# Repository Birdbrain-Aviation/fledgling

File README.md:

# Fledgling

> **Status: work in progress (WIP).** The schematic is drawn and the board is fully routed and passes KiCad's design-rule check (0 errors, 0 unconnected items), but the design is **not reviewed electrically, not fabricated and not tested.** Nothing here has flown. I'm publishing it as it stands.

Fledgling is a small single-MCU flight computer for my model and high-power rockets. It's meant to be a simpler sibling of my CORVID flight computer: the same RP2350 family, IMU and power parts, so firmware and drivers carry over. It is designed to work with the [Aviary](https://github.com/Birdbrain-Aviation/aviary) software suite (Owl ground station, Heron log analysis, Mockingbird hardware-in-the-loop testing).

## Board views

These are rendered from the board file by `tools/render_board.py` (copper, pads and vias only; the inner planes are not drawn), so they are not KiCad screenshots.

## Design intent

These are the goals from my design notes, not verified results.

- Detect launch, burnout and apogee from a barometer and an IMU on one RP2350A
- Fire up to two pyro channels (deployment, backup deployment, or staged-motor ignition)
- Drive two servo outputs on a 5 V rail (airbrakes on my American Rocketry Challenge rocket)
- Log flight data to onboard flash for later analysis in Heron
- Send downlink-only telemetry over an E220 LoRa module (the rocket never receives commands)
- Report status with three LEDs, four addressable RGB LEDs and a buzzer
- Measure a load cell through a 24-bit ADC

Safety approach (as designed, unproven): pyro outputs are held off by gate pull-downs at power-up and reset, pyro has its own battery and a screw arming switch, and firmware ignores pyro until launch is detected.

## Hardware

| | |
|---|---|
| Board | 90 x 40 mm, 4 copper layers (signal / GND / +3V3 / signal), KiCad 10 |
| MCU | RP2350A, W25Q128JVSIQ 16 MB QSPI flash |
| Sensors | MS5611 barometer, LSM6DSO32 IMU, NAU7802 load-cell ADC |
| Radio | E220-900T22D LoRa module (915 MHz) on an 8-pin JST-GH cable |
| Power | Two XT30 battery inputs (main and pyro), two AP63301 buck converters (3.3 V and 5 V), reverse-polarity FET, fuses, TVS diodes |
| Outputs | 2 pyro channels (IRLR7843 low-side MOSFETs), 2 servo headers, 4x WS2812B, buzzer |
| I/O | USB-C, SWD header, I2C OLED header, load-cell header, BOOTSEL and reset buttons |

The schematic has a top-level sheet (`Fledgling.kicad_sch`) and four sub-sheets: Power, IO, Sensors and Pyro. The Pyro sheet is stored in `untitled.kicad_sch`; I left that filename alone so the sheet reference keeps working.

## Repository layout

```
hardware/   KiCad 10 project: schematic sheets, PCB, design rules
  libs/     custom footprint library (Fledgling.pretty)
bom/        parts list exported from my Google Sheet
docs/       DRC report, layout log, remaining-work list, images
tools/      script that renders the board views from the .kicad_pcb
```

Open `hardware/Fledgling.kicad_pro` in KiCad 10.

Symbols and footprints are embedded in the schematic and board files, so the design opens without the extra libraries. To edit parts you'll need the third-party libraries I used, which I haven't redistributed: Raspberry Pi's RP2350 minimal-design KiCad library (`RPI_DB`, `RPI_COMPILED`) and `easyeda2kicad`-converted parts.

## Known state (WIP)

- **2026-11-22: board fully routed, DRC clean.** KiCad 10.0.6 DRC with zones refilled (`docs/DRC-2026-11-22-final.rpt`): **0 errors, 0 unconnected items, 12 warnings.** All 12 warnings are footprint-library mismatches or footprints missing from the `Fledgling` library; they predate the routing. The only part that moved is L1 (0.05 mm in y). The routing was produced with scripts (a grid router and a local checker, not in this repo) and then checked in KiCad, so **nobody has reviewed it electrically**: buck-converter loops, USB pair, QSPI, the ADC dividers and the pyro sense tap still need a human look. Details are in `docs/design-decisions.md` section 11.
- Gerbers and drills for this version are in `fab/Fledgling-gerbers-2026-11-22.zip`. They are DRC-clean but **not yet checked by a fab's CAM or ordered.** Get a quote and a CAM check before ordering.
- The previous version (22 errors / 22 unconnected power connections) is kept in `hardware/archive/Fledgling_routed_2026-11-21.kicad_pcb`.
- Changes on 2026-11-17: E220 supply (J2 pin 6) moved from +5V to +3V3, with the +5V trunk re-routed under J2 on B.Cu; C35/C36 feed-forward capacitor values set. See `docs/design-decisions.md`.
- Connector orientation (USB-C and XT30) checked. See `docs/layout-log-2026-11-14.md` and `docs/design-decisions.md` for the full history.
- The BOM is a draft. Some prices are optimistic LCSC "from" prices, some parts are marked pending (pyro fuse rating, load cell capacity), and a few parts have low stock. See the Status and Notes columns in `bom/Fledgling_BOM.csv`.
- Routing is complete but machine-generated and untidy in places (many small jogs near the RP2350).
- The design has changed since my first sketches (it started as a 30 x 80 mm 2-layer board), so the early notes don't all match the current board.

## License

Not yet specified.

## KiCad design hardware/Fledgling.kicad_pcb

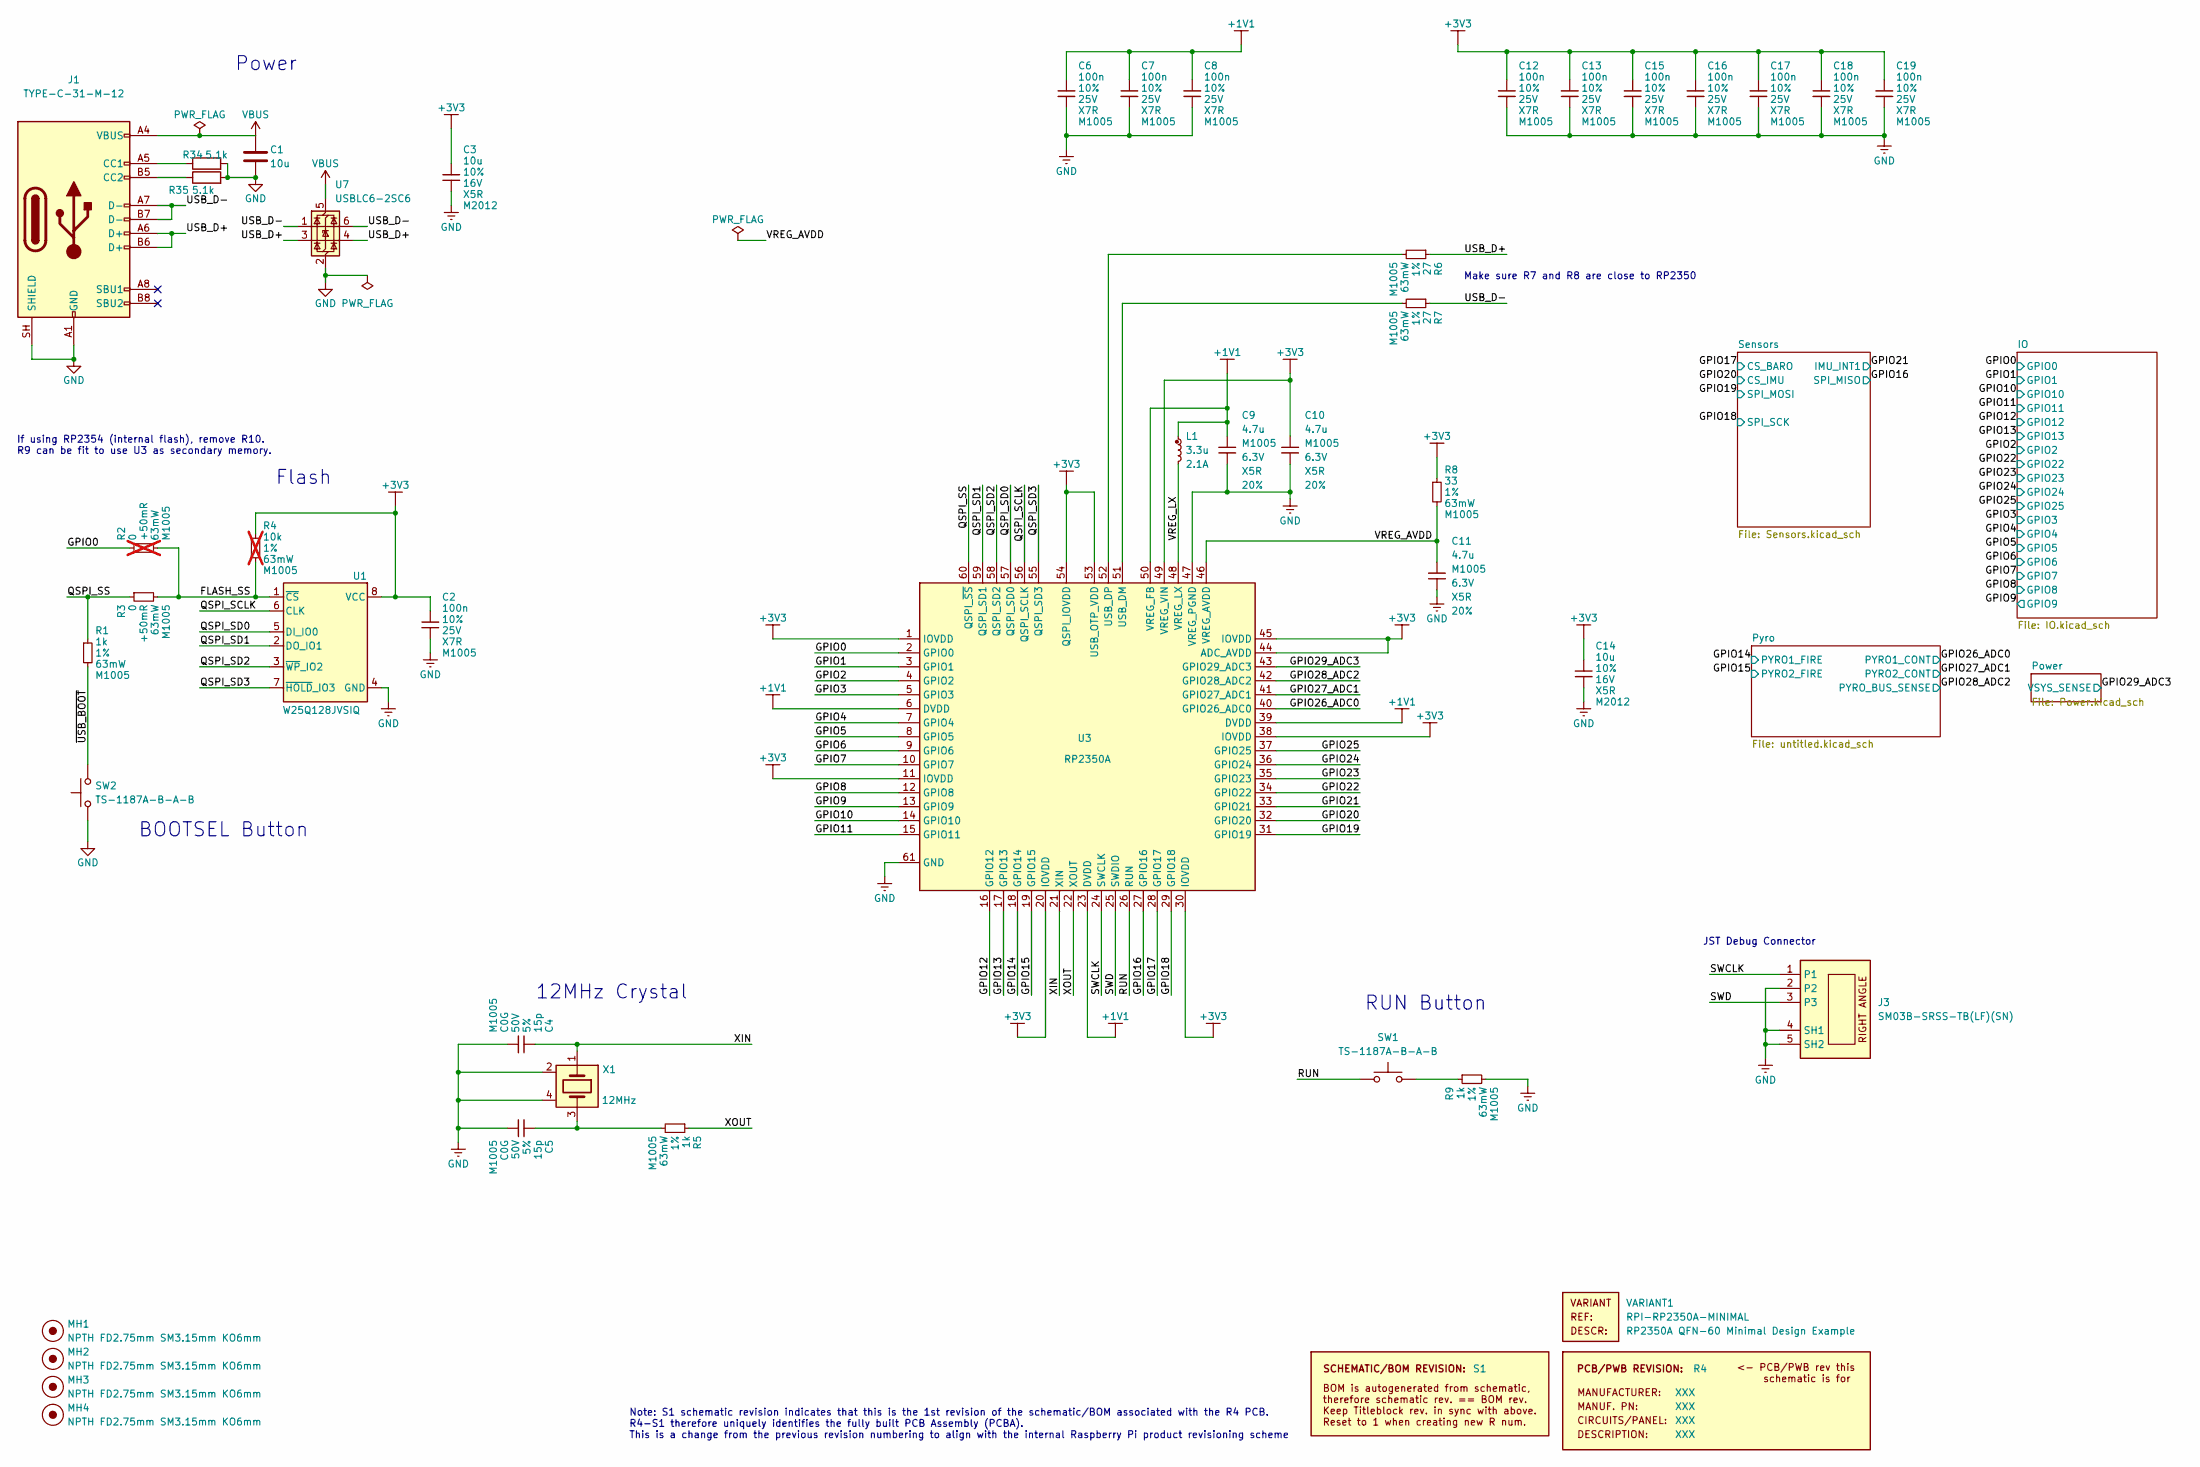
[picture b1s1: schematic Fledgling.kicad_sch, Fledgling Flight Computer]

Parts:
C1: 10u; C_0805_2012Metric; LCSC Part C15850
C2, C6, C7, C8, C12, C13, C15, C16, C17, C18, C19: 100n; generic_capc1005x50; voltage 25V; tolerance 10%; part_uid RP-01BJ9Y-KRGF41; lcsc_pn C77014
C3, C14: 10u; generic_capc2012x125; voltage 16V; tolerance 10%; part_uid RP-01GYSK-AVBE41; lcsc_pn C77075
C4, C5: 15p; generic_capc1005x50; voltage 50V; tolerance 5%; part_uid RP-01C89W-LLY9XV; lcsc_pn C76950
C9, C10: 4.7u; generic_capc1005x50_wide; voltage 6.3V; tolerance 20%; part_uid RP-019A1P-0C2GHY; lcsc_pn C82453
C11: 4.7u; generic_capc1005x50; voltage 6.3V; tolerance 20%; part_uid RP-019A1P-0C2GHY; lcsc_pn C82453
J1: TYPE-C-31-M-12; USB_C_Receptacle_HRO_TYPE-C-31-M-12; LCSC Part C165948
J3: SM03B-SRSS-TB(LF)(SN); jst_sm03b-srss-tb-lf--sn-; part_uid RP-01EKJ1-8V9SV1; LCSC Part C3029342
L1: 3.3u; abracon_aota-b201610s3r3-101-t; tolerance 20%; part_uid RP-01GY5D-2VC7WP; lcsc_pn C42411119
MH1, MH2, MH3, MH4: NPTH FD2.75mm SM3.15mm KO6mm; none_mh_npth_fd2p75mm_sm3p15mm_ko6mm; part_uid RP-01HF5R-LCTEJS
PCB1: R4; manufacturer_pn XXX
R1, R5, R9: 1k; generic_resc1005x35; tolerance 1%; voltage 50V; part_uid RP-019A1P-4Z6ZWY; lcsc_pn C106235
R2: 0; generic_resc1005x35; tolerance +50mR; voltage 50V; part_uid RP-019A1P-4Y4V63; lcsc_pn C60485; not fitted
R3: 0; generic_resc1005x35; tolerance +50mR; voltage 50V; part_uid RP-019A1P-4Y4V63; lcsc_pn C60485
R4: 10k; generic_resc1005x35; tolerance 1%; voltage 50V; part_uid RP-019A1P-53DHSX; lcsc_pn C60490; not fitted
R6, R7: 27; generic_resc1005x35; tolerance 1%; voltage 50V; part_uid RP-01C89V-LTEYC4; lcsc_pn C138021
R8: 33; generic_resc1005x35; tolerance 1%; voltage 50V; part_uid RP-019A1P-58PW9L; lcsc_pn C138002
R34, R35: 5.1k; R_0603_1608Metric; LCSC Part C23186
SBREV1: S1
SW1, SW2: TS-1187A-B-A-B; SW_Push_1P1T_XKB_TS-1187A; LCSC Part C318884
U1: W25Q128JVSIQ; generic_soic127p790x195-8; voltage 2.7-3.6V; part_uid RP-01JWD4-F1H4N9; lcsc_pn C97521
U3: RP2350A; rpi_rp2350a_vias; part_uid RP-01HA9H-9K5E8T; lcsc_pn C42411118
U7: USBLC6-2SC6; SOT-23-6; LCSC Part C7519
VARIANT1: RPI-RP2350A-MINIMAL
X1: 12MHz; generic_xtalcc320x250x80-4; tolerance 30ppm; part_uid RP-01G8X7-GS352B; lcsc_pn C20625731

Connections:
+1V1: C6.1, C7.1, C8.1, C9.1, L1.1, U3.6 (DVDD), U3.23 (DVDD), U3.39 (DVDD), U3.50 (VREG_FB)
+3V3: C2.1, C3.1, C10.1, C12.1, C13.1, C14.1, C15.1, C16.1, C17.1, C18.1, C19.1, R4.1, R8.1, U1.8 (VCC), U3.1 (IOVDD), U3.11 (IOVDD), U3.20 (IOVDD), U3.30 (IOVDD), U3.38 (IOVDD), U3.44 (ADC_AVDD), U3.45 (IOVDD), U3.49 (VREG_VIN), U3.53 (USB_OTP_VDD), U3.54 (QSPI_IOVDD); also elsewhere on the board
/FLASH_SS: R2.2, R3.2, R4.2, U1.1 (~CS)
/GPIO0: R2.1, U3.2 (GPIO0); also elsewhere on the board
/GPIO1: U3.3 (GPIO1); also elsewhere on the board
/GPIO2: U3.4 (GPIO2); also elsewhere on the board
/GPIO3: U3.5 (GPIO3); also elsewhere on the board
/GPIO4: U3.7 (GPIO4); also elsewhere on the board
/GPIO5: U3.8 (GPIO5); also elsewhere on the board
/GPIO6: U3.9 (GPIO6); also elsewhere on the board
/GPIO7: U3.10 (GPIO7); also elsewhere on the board
/GPIO8: U3.12 (GPIO8); also elsewhere on the board
/GPIO9: U3.13 (GPIO9); also elsewhere on the board
/GPIO10: U3.14 (GPIO10); also elsewhere on the board
/GPIO11: U3.15 (GPIO11); also elsewhere on the board
/GPIO12: U3.16 (GPIO12); also elsewhere on the board
/GPIO13: U3.17 (GPIO13); also elsewhere on the board
/GPIO14: U3.18 (GPIO14); also elsewhere on the board
/GPIO15: U3.19 (GPIO15); also elsewhere on the board
/GPIO16: U3.27 (GPIO16); also elsewhere on the board
/GPIO17: U3.28 (GPIO17); also elsewhere on the board
/GPIO18: U3.29 (GPIO18); also elsewhere on the board
/GPIO19: U3.31 (GPIO19); also elsewhere on the board
/GPIO20: U3.32 (GPIO20); also elsewhere on the board
/GPIO21: U3.33 (GPIO21); also elsewhere on the board
/GPIO22: U3.34 (GPIO22); also elsewhere on the board
/GPIO23: U3.35 (GPIO23); also elsewhere on the board
/GPIO24: U3.36 (GPIO24); also elsewhere on the board
/GPIO25: U3.37 (GPIO25); also elsewhere on the board
/GPIO26_ADC0: U3.40 (GPIO26_ADC0); also elsewhere on the board
/GPIO27_ADC1: U3.41 (GPIO27_ADC1); also elsewhere on the board
/GPIO28_ADC2: U3.42 (GPIO28_ADC2); also elsewhere on the board
/GPIO29_ADC3: U3.43 (GPIO29_ADC3); also elsewhere on the board
/QSPI_SCLK: U1.6 (CLK), U3.56 (QSPI_SCLK)
/QSPI_SD0: U1.5 (DI_IO0), U3.57 (QSPI_SD0)
/QSPI_SD1: U1.2 (DO_IO1), U3.59 (QSPI_SD1)
/QSPI_SD2: U1.3 (~WP_IO2), U3.58 (QSPI_SD2)
/QSPI_SD3: U1.7 (~HOLD_IO3), U3.55 (QSPI_SD3)
/QSPI_SS: R1.1, R3.1, U3.60 (QSPI_~SS)
/RUN: SW1.1, U3.26 (RUN)
/SWCLK: J3.1, U3.24 (SWCLK)
/SWD: J3.3, U3.25 (SWDIO)
/USB_D+: J1.A6 (D+), J1.B6 (D+), R6.1, U7.3 (I/O2), U7.4 (I/O2)
/USB_D-: J1.A7 (D-), J1.B7 (D-), R7.1, U7.1 (I/O1), U7.6 (I/O1)
/VREG_AVDD: C11.1, R8.2, U3.46 (VREG_AVDD)
/VREG_LX: L1.2, U3.48 (VREG_LX)
/XIN: C4.1, U3.21 (XIN), X1.1
/XOUT: R5.1, U3.22 (XOUT)
/~USB_BOOT: R1.2, SW2.2
GND: C1.2, C2.2, C3.2, C4.2, C5.2, C6.2, C7.2, C8.2, C9.2, C10.2, C11.2, C12.2, C13.2, C14.2, C15.2, C16.2, C17.2, C18.2, C19.2, J1.A1 (GND), J1.A12 (GND), J1.B1 (GND), J1.B12 (GND), J1.SH (SHIELD), J3.2, J3.4 (SH1), J3.5 (SH2), R9.2, R34.2, R35.2, SW2.1, U1.4 (GND), U3.47 (VREG_PGND), U3.61 (GND), U7.2 (GND), X1.2, X1.4; also elsewhere on the board
unnamed: C5.1, R5.2, X1.3
unnamed: J1.A5 (CC1), R34.1
unnamed: J1.B5 (CC2), R35.1
unnamed: R9.1, SW1.2
unnamed: R7.2, U3.51 (USB_DM)
unnamed: R6.2, U3.52 (USB_DP)
VBUS: C1.1, J1.A4 (VBUS), J1.A9 (VBUS), J1.B4 (VBUS), J1.B9 (VBUS), U7.5 (VBUS); also elsewhere on the board

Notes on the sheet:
JST Debug Connector
RUN Button
BOOTSEL Button
If using RP2354 (internal flash), remove R10. R9 can be fit to use U3 as secondary memory.
Flash
Note: S1 schematic revision indicates that this is the 1st revision of the schematic/BOM associated with the R4 PCB. R4-S1 therefore uniquely identifies the fully built PCB Assembly (PCBA). This is a change from the previous revision numbering to align with the internal Raspberry Pi product revisio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
Make sure R7 and R8 are close to RP2350
12MHz Crystal
Power

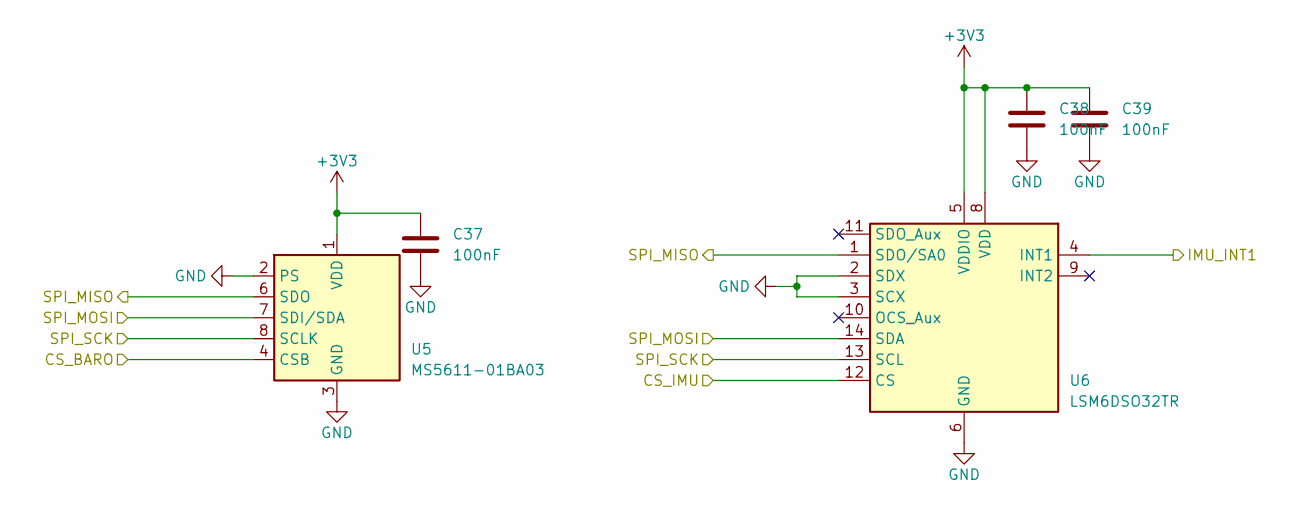
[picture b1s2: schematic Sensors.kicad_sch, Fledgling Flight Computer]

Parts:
C37, C38, C39: 100nF; C_0603_1608Metric; LCSC Part C1591
U5: MS5611-01BA03; LGA-8_3x5mm_P1.25mm; MPN MS561101BA03-50; LCSC Part C15639
U6: LSM6DSO32TR; LGA-14_3x2.5mm_P0.5mm_LayoutBorder3x4y; LCSC Part C1864162

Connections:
+3V3: C37.1, C38.1, C39.1, U5.1 (VDD), U6.5 (VDDIO), U6.8 (VDD); also elsewhere on the board
/GPIO16: U5.6 (SDO), U6.1 (SDO/SA0); also elsewhere on the board
/GPIO17: U5.4 (CSB), U5.5 (CSB); also elsewhere on the board
/GPIO18: U5.8 (SCLK), U6.13 (SCL); also elsewhere on the board
/GPIO19: U5.7 (SDI/SDA), U6.14 (SDA); also elsewhere on the board
/GPIO20: U6.12 (CS); also elsewhere on the board
/GPIO21: U6.4 (INT1); also elsewhere on the board
GND: C37.2, C38.2, C39.2, U5.2 (PS), U5.3 (GND), U6.2 (SDX), U6.3 (SCX), U6.6 (GND), U6.7 (GND); also elsewhere on the board

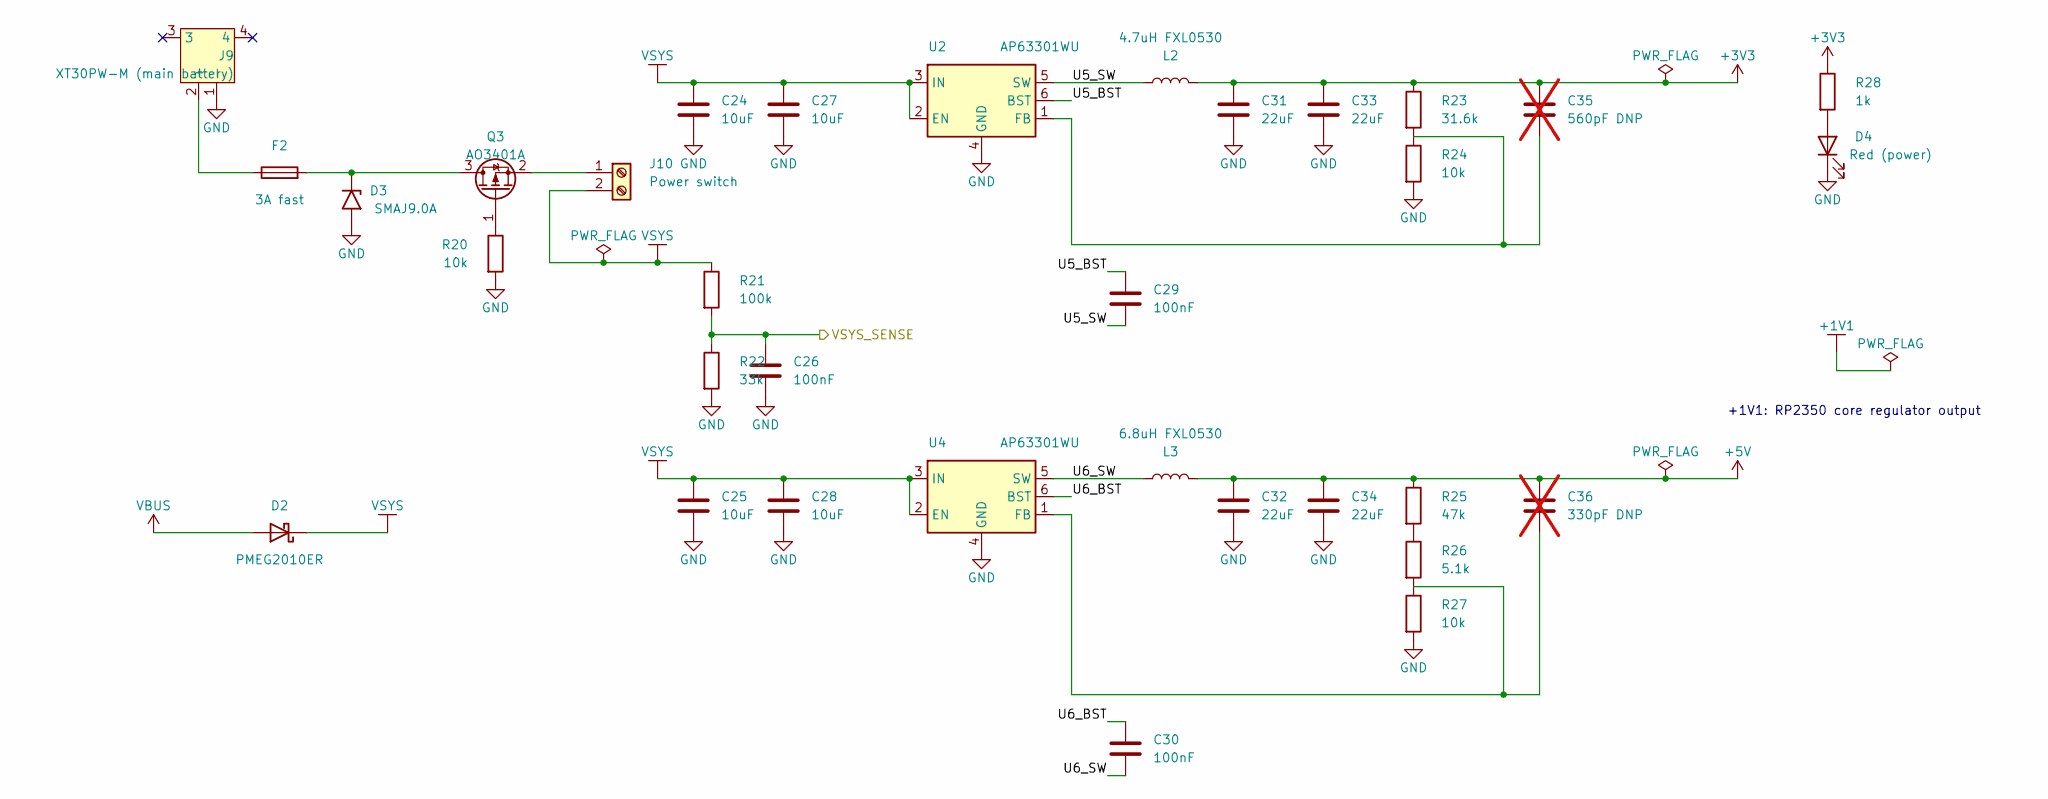
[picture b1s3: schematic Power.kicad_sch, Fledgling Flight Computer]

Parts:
C24, C25, C27, C28: 10uF; C_0805_2012Metric; Voltage 25V; LCSC Part C15850
C26, C29, C30: 100nF; C_0603_1608Metric; LCSC Part C1591
C31, C32, C33, C34: 22uF; C_0805_2012Metric; Voltage 10V; LCSC Part C92814
C35: 560pF DNP; C_0603_1608Metric; LCSC Part C55393; not fitted
C36: 330pF DNP; C_0603_1608Metric; LCSC Part C1664; not fitted
D2: PMEG2010ER; Nexperia_CFP3_SOD-123W; LCSC Part C82288
D3: SMAJ9.0A; D_SMA; LCSC Part C113955
D4: Red (power); LED_0603_1608Metric; LCSC Part C2286
F2: 3A fast; Fuse_1206_3216Metric; MPN 0466003.NRHF; LCSC Part C14165
J9: XT30PW-M (main battery); CONN-TH_XT30PW-M; MPN XT30PW-M30.G.Y; LCSC Part C431092
J10: Power switch; TerminalBlock_Phoenix_MKDS-1-2-3.81_1x02_P3.81mm_Horizontal; LCSC Part C395878
L2: 4.7uH FXL0530; L_Changjiang_FXL0530; LCSC Part C177246
L3: 6.8uH FXL0530; L_Changjiang_FXL0530; LCSC Part C177249
Q3: AO3401A; SOT-23; LCSC Part C347476
R20, R24, R27: 10k; R_0603_1608Metric; LCSC Part C25804
R21: 100k; R_0603_1608Metric; LCSC Part C25803
R22: 33k; R_0603_1608Metric; LCSC Part C4216
R23: 31.6k; R_0603_1608Metric; LCSC Part C25967
R25: 47k; R_0603_1608Metric; LCSC Part C25819
R26: 5.1k; R_0603_1608Metric; LCSC Part C23186
R28: 1k; R_0603_1608Metric; LCSC Part C21190
U2, U4: AP63301WU; TSOT-23-6; LCSC Part C2158003

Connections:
+3V3: C31.1, C33.1, C35.1, L2.2, R23.1, R28.1; also elsewhere on the board
+5V: C32.1, C34.1, C36.1, L3.2, R25.1; also elsewhere on the board
/GPIO29_ADC3: C26.1, R21.2, R22.1; also elsewhere on the board
/Power/U5_BST: C29.1, U2.6 (BST)
/Power/U5_SW: C29.2, L2.1, U2.5 (SW)
/Power/U6_BST: C30.1, U4.6 (BST)
/Power/U6_SW: C30.2, L3.1, U4.5 (SW)
GND: C24.2, C25.2, C26.2, C27.2, C28.2, C31.2, C32.2, C33.2, C34.2, D3.2 (A2), D4.1 (K), J9.1 (-), R20.2, R22.2, R24.2, R27.2, U2.4 (GND), U4.4 (GND); also elsewhere on the board
unnamed: D3.1 (A1), F2.2, Q3.3 (D)
unnamed: D4.2 (A), R28.2
unnamed: F2.1, J9.2 (+)
unnamed: J10.1, Q3.2 (S)
unnamed: Q3.1 (G), R20.1
unnamed: R25.2, R26.1
unnamed: C35.2, R23.2, R24.1, U2.1 (FB)
unnamed: C36.2, R26.2, R27.1, U4.1 (FB)
VBUS: D2.2 (A); also elsewhere on the board
VSYS: C24.1, C25.1, C27.1, C28.1, D2.1 (K), J10.2, R21.1, U2.2 (EN), U2.3 (IN), U4.2 (EN), U4.3 (IN)

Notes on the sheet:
+1V1: RP2350 core regulator output

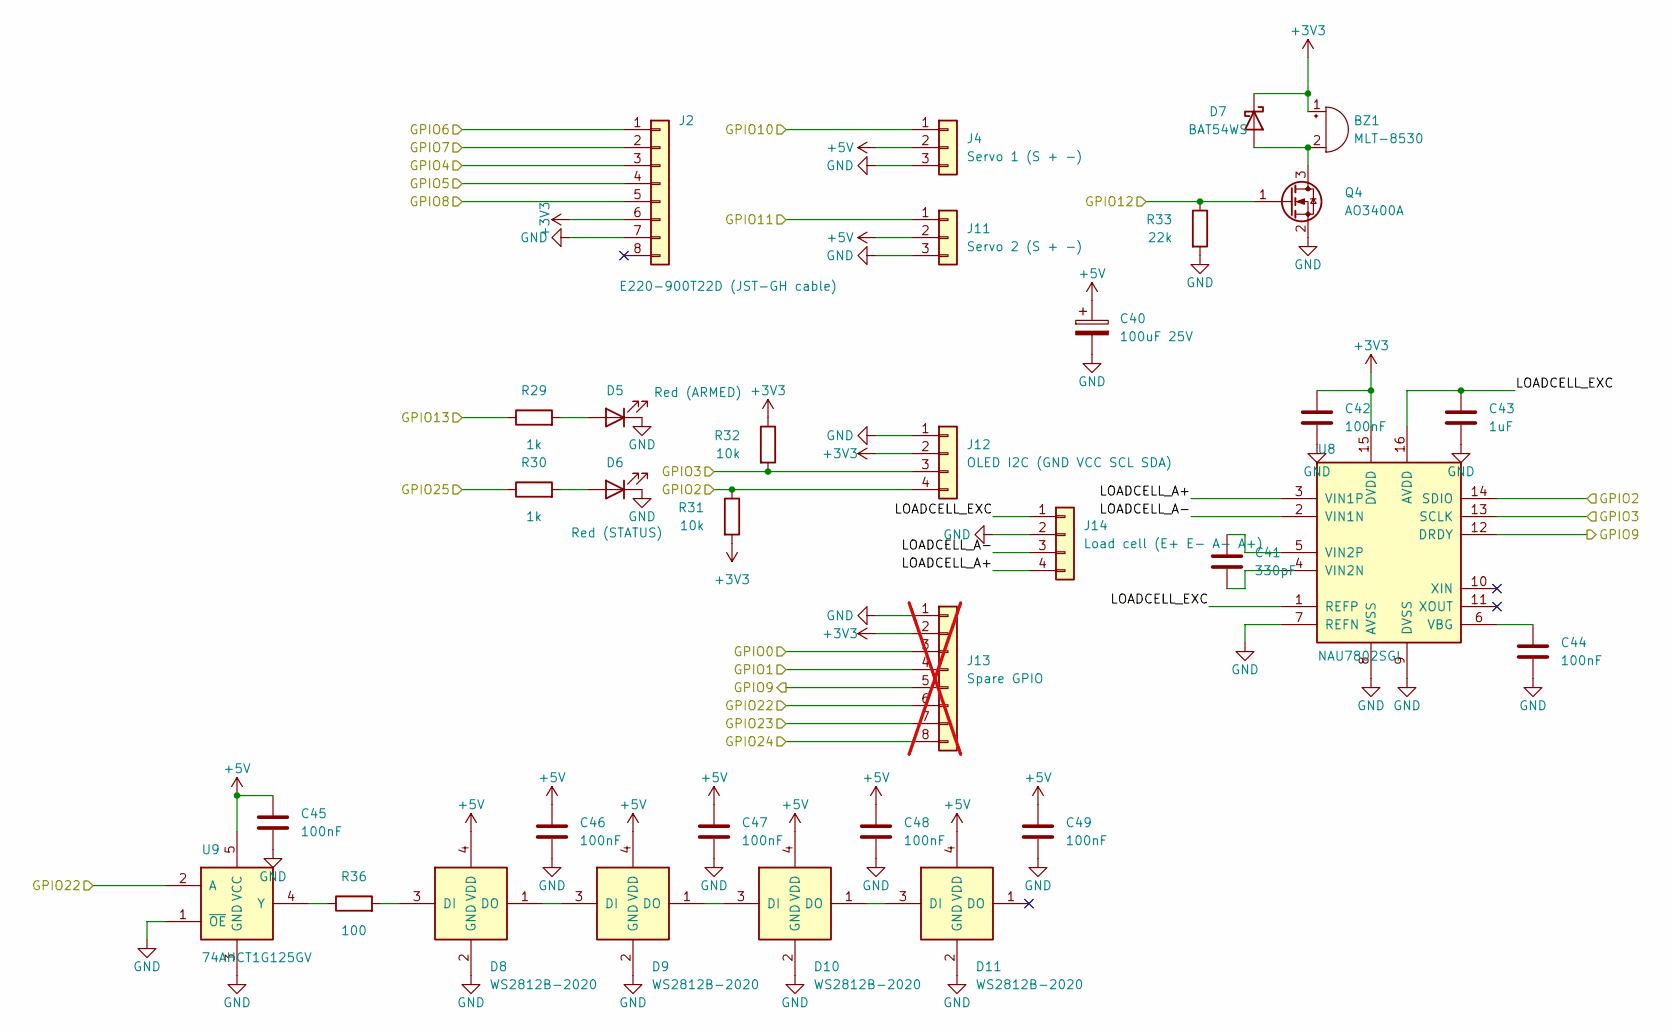
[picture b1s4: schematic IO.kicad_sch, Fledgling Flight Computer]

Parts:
BZ1: MLT-8530; Buzzer_Huaneng_MLT-8530; LCSC Part C94599
C40: 100uF 25V; CP_Elec_6.3x7.7; LCSC Part C72477
C41: 330pF; C_0603_1608Metric; LCSC Part C1664
C42, C44, C45, C46, C47, C48, C49: 100nF; C_0603_1608Metric; LCSC Part C1591
C43: 1uF; C_0603_1608Metric; LCSC Part C95843
D5: Red (ARMED); LED_0603_1608Metric; LCSC Part C2286
D6: Red (STATUS); LED_0603_1608Metric; LCSC Part C2286
D7: BAT54WS; D_SOD-323; LCSC Part C191198
D8, D9, D10, D11: WS2812B-2020; LED_WS2812B-2020_PLCC4_2.0x2.0mm; LCSC Part C965555
J2: E220-900T22D (JST-GH cable); JST_GH_SM08B-GHS-TB_1x08-1MP_P1.25mm_Horizontal; LCSC Part C265111
J4: Servo 1 (S + -); JST_GH_SM03B-GHS-TB_1x03-1MP_P1.25mm_Horizontal; LCSC Part C514175
J11: Servo 2 (S + -); JST_GH_SM03B-GHS-TB_1x03-1MP_P1.25mm_Horizontal; LCSC Part C514175
J12: OLED I2C (GND VCC SCL SDA); JST_GH_SM04B-GHS-TB_1x04-1MP_P1.25mm_Horizontal; LCSC Part C189895
J13: Spare GPIO; PinHeader_1x08_P1.27mm_Vertical; not fitted
J14: Load cell (E+ E- A- A+); JST_GH_SM04B-GHS-TB_1x04-1MP_P1.25mm_Horizontal; LCSC Part C189895
Q4: AO3400A; SOT-23; LCSC Part C347475
R29, R30: 1k; R_0603_1608Metric; LCSC Part C21190
R31, R32: 10k; R_0603_1608Metric; LCSC Part C25804
R33: 22k; R_0603_1608Metric; LCSC Part C31850
R36: 100; R_0603_1608Metric; LCSC Part C22775
U8: NAU7802SGI; SOIC-16_3.9x9.9mm_P1.27mm; LCSC Part C2614351
U9: 74AHCT1G125GV; SOT-23-5; LCSC Part C12494

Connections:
+3V3: BZ1.1 (+), C42.1, D7.1 (K), J2.6, J12.2, J13.2, R31.2, R32.1, U8.15 (DVDD); also elsewhere on the board
+5V: C40.1, C45.1, C46.1, C47.1, C48.1, C49.1, D8.4 (VDD), D9.4 (VDD), D10.4 (VDD), D11.4 (VDD), J4.2, J11.2, U9.5 (VCC); also elsewhere on the board
/GPIO0: J13.3; also elsewhere on the board
/GPIO1: J13.4; also elsewhere on the board
/GPIO2: J12.4, R31.1, U8.14 (SDIO); also elsewhere on the board
/GPIO3: J12.3, R32.2, U8.13 (SCLK); also elsewhere on the board
/GPIO4: J2.3; also elsewhere on the board
/GPIO5: J2.4; also elsewhere on the board
/GPIO6: J2.1; also elsewhere on the board
/GPIO7: J2.2; also elsewhere on the board
/GPIO8: J2.5; also elsewhere on the board
/GPIO9: J13.5, U8.12 (DRDY); also elsewhere on the board
/GPIO10: J4.1; also elsewhere on the board
/GPIO11: J11.1; also elsewhere on the board
/GPIO12: Q4.1 (G), R33.1; also elsewhere on the board
/GPIO13: R29.1; also elsewhere on the board
/GPIO22: J13.6, U9.2 (A); also elsewhere on the board
/GPIO23: J13.7; also elsewhere on the board
/GPIO24: J13.8; also elsewhere on the board
/GPIO25: R30.1; also elsewhere on the board
/IO/LOADCELL_A+: J14.4, U8.3 (VIN1P)
/IO/LOADCELL_A-: J14.3, U8.2 (VIN1N)
/IO/LOADCELL_EXC: C43.1, J14.1, U8.1 (REFP), U8.16 (AVDD)
GND: C40.2, C42.2, C43.2, C44.2, C45.2, C46.2, C47.2, C48.2, C49.2, D5.1 (K), D6.1 (K), D8.2 (GND), D9.2 (GND), D10.2 (GND), D11.2 (GND), J2.7, J4.3, J11.3, J12.1, J13.1, J14.2, Q4.2 (S), R33.2, U8.7 (REFN), U8.8 (AVSS), U8.9 (DVSS), U9.1 (~OE), U9.3 (GND); also elsewhere on the board
unnamed: BZ1.2 (-), D7.2 (A), Q4.3 (D)
unnamed: D5.2 (A), R29.2
unnamed: D6.2 (A), R30.2
unnamed: D8.3 (DI), R36.2
unnamed: D8.1 (DO), D9.3 (DI)
unnamed: D9.1 (DO), D10.3 (DI)
unnamed: D10.1 (DO), D11.3 (DI)
unnamed: C44.1, U8.6 (VBG)
unnamed: C41.2, U8.4 (VIN2N)
unnamed: C41.1, U8.5 (VIN2P)
unnamed: R36.1, U9.4 (Y)

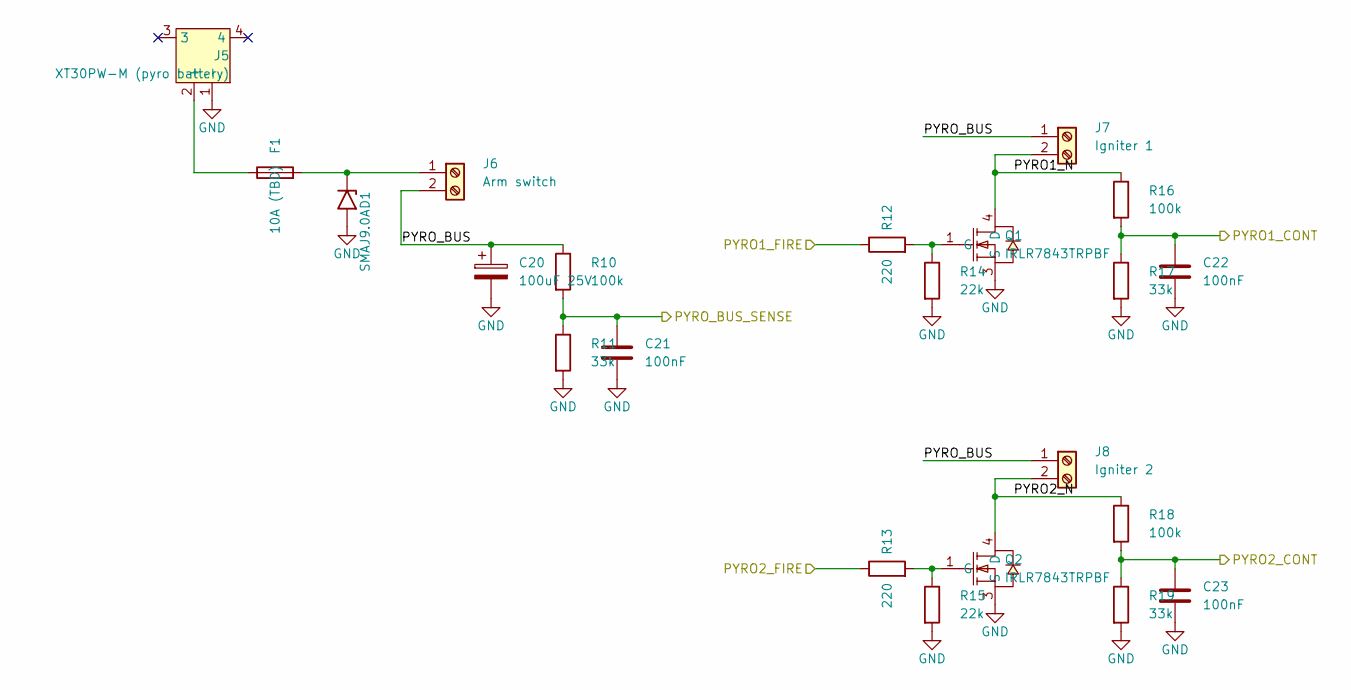
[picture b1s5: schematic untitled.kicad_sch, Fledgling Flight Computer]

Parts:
C20: 100uF 25V; CP_Elec_6.3x7.7; LCSC Part C72477
C21, C22, C23: 100nF; C_0603_1608Metric; LCSC Part C1591
D1: SMAJ9.0A; D_SMA; LCSC Part C113955
F1: 10A (TBD); Fuse_1206_3216Metric; LCSC Part C136354
J5: XT30PW-M (pyro battery); CONN-TH_XT30PW-M; MPN XT30PW-M30.G.Y; LCSC Part C431092
J6: Arm switch; TerminalBlock_Phoenix_MKDS-1-2-3.81_1x02_P3.81mm_Horizontal; LCSC Part C395878
J7: Igniter 1; TerminalBlock_Phoenix_MKDS-1-2-3.81_1x02_P3.81mm_Horizontal; LCSC Part C395878
J8: Igniter 2; TerminalBlock_Phoenix_MKDS-1-2-3.81_1x02_P3.81mm_Horizontal; LCSC Part C395878
Q1, Q2: IRLR7843TRPBF; TO-252-2_L6.5-W6.1-P4.58-LS10.0-TR; MPN IRLR7843TRPBF; LCSC Part C21988
R10, R16, R18: 100k; R_0603_1608Metric; LCSC Part C25803
R11, R17, R19: 33k; R_0603_1608Metric; LCSC Part C4216
R12, R13: 220; R_0603_1608Metric; LCSC Part C22962
R14, R15: 22k; R_0603_1608Metric; LCSC Part C31850

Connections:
/GPIO14: R12.1; also elsewhere on the board
/GPIO15: R13.1; also elsewhere on the board
/GPIO26_ADC0: C22.1, R16.2, R17.1; also elsewhere on the board
/GPIO27_ADC1: C23.1, R18.2, R19.1; also elsewhere on the board
/GPIO28_ADC2: C21.1, R10.2, R11.1; also elsewhere on the board
/Pyro/PYRO1_N: J7.2, Q1.4 (D), R16.1
/Pyro/PYRO2_N: J8.2, Q2.4 (D), R18.1
/Pyro/PYRO_BUS: C20.1, J6.2, J7.1, J8.1, R10.1
GND: C20.2, C21.2, C22.2, C23.2, D1.2 (A2), J5.1 (-), Q1.3 (S), Q2.3 (S), R11.2, R14.2, R15.2, R17.2, R19.2; also elsewhere on the board
unnamed: D1.1 (A1), F1.2, J6.1
unnamed: F1.1, J5.2 (+)
unnamed: Q1.1 (G), R12.2, R14.1
unnamed: Q2.1 (G), R13.2, R15.1
